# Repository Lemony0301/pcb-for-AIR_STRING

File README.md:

# AIR_STRING pcb
pcb for air string from chuni arcade

## Information
this pcb is designed based on CrazyRedMachine's chunithmIO

that site <https://github.com/CrazyRedMachine/ChunithmIO>

## Pin Out
if u order the pcbs i designed, you need to change the code

check the pin and change them

|PCB|Ardunio|
|:-:|:-----:|
|out1|4|
|out2|5|
|out3|6|
|out4|7|
|out5|8|
|out6|9|
|Dat1|18|
|Dat2|19|

## Parts Required
- 1x arduino pro micro
- 2x any 12x1 pin header socket(2.54mm)
- 4x B6B-XH-A(jst)
- 2x b3b-XH-A(jst)
- 1x b2b-XH-A(jst)

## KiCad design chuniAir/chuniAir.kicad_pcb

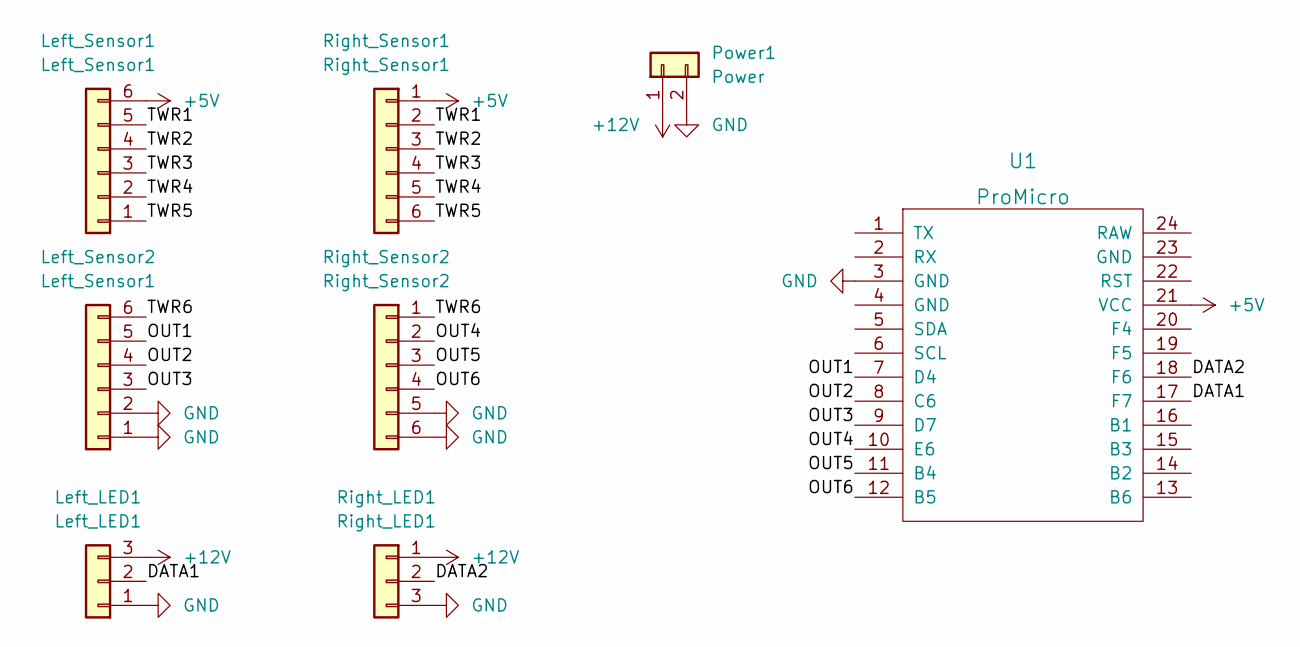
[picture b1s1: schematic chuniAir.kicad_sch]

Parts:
Left_LED1: Left_LED1; JST_XH_B3B-XH-A_1x03_P2.50mm_Vertical
Left_Sensor1, Left_Sensor2: Left_Sensor1; JST_XH_B6B-XH-A_1x06_P2.50mm_Vertical
Power1: Power; JST_XH_B2B-XH-A_1x02_P2.50mm_Vertical
Right_LED1: Right_LED1; JST_XH_B3B-XH-A_1x03_P2.50mm_Vertical
Right_Sensor1: Right_Sensor1; JST_XH_B6B-XH-A_1x06_P2.50mm_Vertical
Right_Sensor2: Right_Sensor2; JST_XH_B6B-XH-A_1x06_P2.50mm_Vertical
U1: ProMicro; ProMicro-EnforcedTop

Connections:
+5V: Left_Sensor1.6, Right_Sensor1.1, U1.21 (VCC)
+12V: Left_LED1.3, Power1.1, Right_LED1.1
/DATA1: Left_LED1.2, U1.17 (F7)
/DATA2: Right_LED1.2, U1.18 (F6)
/OUT1: Left_Sensor2.5, U1.7 (D4)
/OUT2: Left_Sensor2.4, U1.8 (C6)
/OUT3: Left_Sensor2.3, U1.9 (D7)
/OUT4: Right_Sensor2.2, U1.10 (E6)
/OUT5: Right_Sensor2.3, U1.11 (B4)
/OUT6: Right_Sensor2.4, U1.12 (B5)
/TWR1: Left_Sensor1.5, Right_Sensor1.2
/TWR2: Left_Sensor1.4, Right_Sensor1.3
/TWR3: Left_Sensor1.3, Right_Sensor1.4
/TWR4: Left_Sensor1.2, Right_Sensor1.5
/TWR5: Left_Sensor1.1, Right_Sensor1.6
/TWR6: Left_Sensor2.6, Right_Sensor2.1
GND: Left_LED1.1, Left_Sensor2.1, Left_Sensor2.2, Power1.2, Right_LED1.3, Right_Sensor2.5, Right_Sensor2.6, U1.3 (GND)

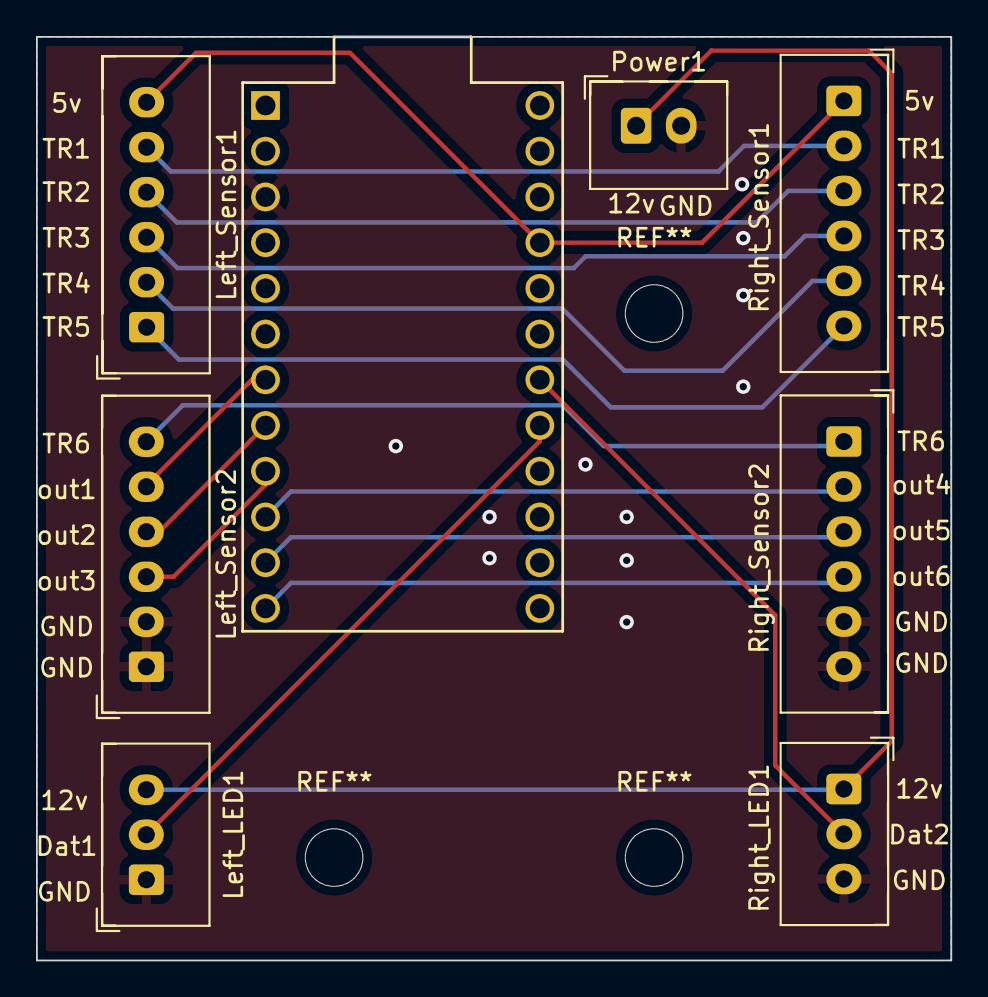
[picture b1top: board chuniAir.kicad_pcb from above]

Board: 2 copper layers, 50.8 x 51.3 mm, 8 parts (0 on the bottom side), 17 nets.
